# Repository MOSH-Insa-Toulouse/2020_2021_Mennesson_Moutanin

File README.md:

# Kicad Practical TP / Communicating gas sensor

## KiCad - Shield for Arduino

### TODO Kicad

- [x] Create Kicad project
- [x] Design the circuit board
- [x] Assign the components footprints
- [x] Design of the pcb
- [x] Component placement
- [x] Routing

### Diagram

### Placement and Routing

### 3D View

## Manufacturing and integration of nano-technology sensors

You'll find a datasheet related to the sensor we integrated under >A.I.M.E  

It has been done by Zheng Zhou, Terence Liew, Brice Moutanin and Baptiste Mennesson

## Analog Electronic Labs

The goal of this part was to simulate our sensor and its associated electronic diagram thanks to LTSpice. In order to obtain the cutoff frequencies of the different steps and observe the noise attenuations at 50kHz and at the Nyquist frequency.

### Electronic Diagram

### Gas Sensor

### Characteristics

## Analog Electronic Labs

This part was focused on exploiting the data from the gas sensor. The idea was to interconnect several technologies; recover the data from the sensor using an arduino, process this data with the Arduino software, send it over the LoRa network, retrieve it on The Things Network, and finally display it on a dashboard thanks to a Node-Red flow.  

You'll find all the related files under >MOSH>LoRa_Small_Project

### Node-Red Flow Example (Temperature Data)

### Dashboard Example (Temperature Data)

## Contribution

### Students 

* Baptiste MENNESSON
* Brice MOUTANIN

### Tutors

* Jérémie GRISOLIA
* Arnauld BIGANZOLI 
* Benjamin MESTRE

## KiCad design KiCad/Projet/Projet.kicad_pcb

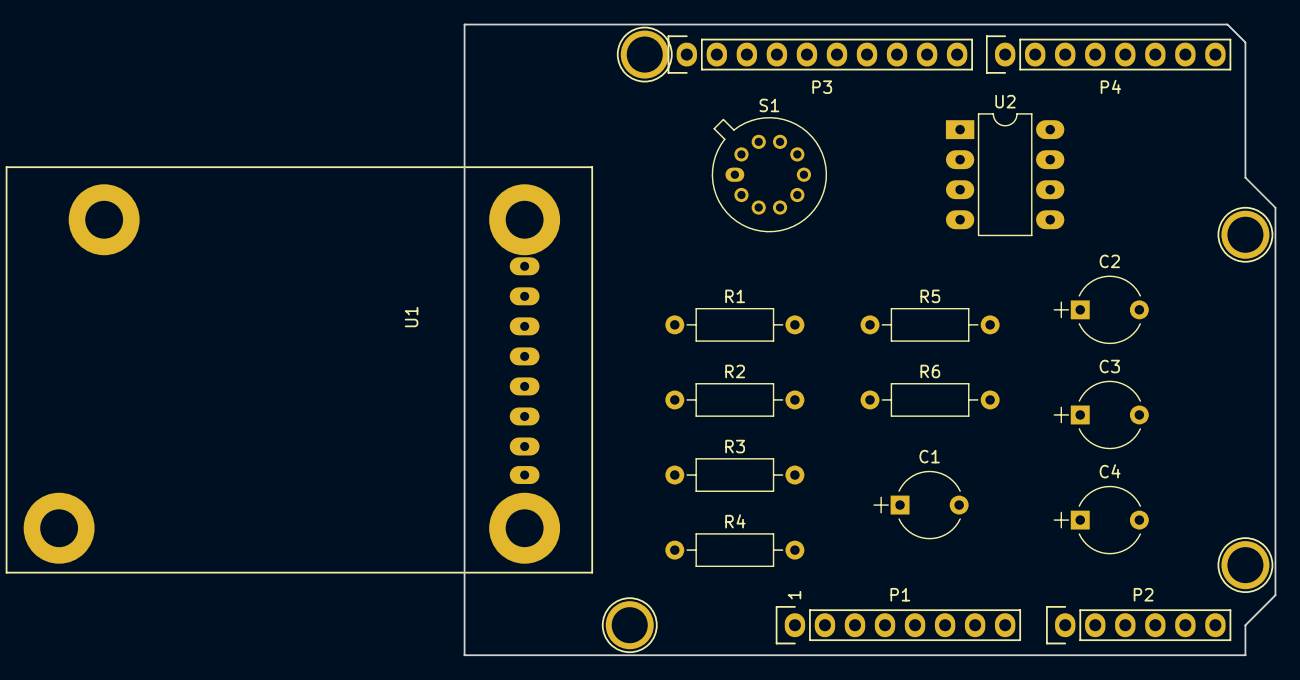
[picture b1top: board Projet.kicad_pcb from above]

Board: 2 copper layers, 68.6 x 53.3 mm, 21 parts (0 on the bottom side), 3 nets, no tracks yet.

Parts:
C1, C2, C3, C4: CP_Radial_Tantal_D5.5mm_P5.00mm
P1: Power; Socket_Strip_Arduino_1x08
P2: Analog; Socket_Strip_Arduino_1x06
P3: Digital; Socket_Strip_Arduino_1x10
P4: Digital; Socket_Strip_Arduino_1x08
P5, P6, P7, P8: CONN_01X01; Arduino_1pin
R1, R2, R3, R4, R5, R6: R_Axial_DIN0207_L6.3mm_D2.5mm_P10.16mm_Horizontal
S1: TO-5-10_Window; Empreinte_Capteur_Gaz
U1: RN2483_breakout
U2: DIP-8_W7.62mm_LongPads; Package_DIP-8_W7.62mm_LongPads

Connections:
/A4(SDA): P2.5, P3.2
/A5(SCL): P2.6, P3.1
GND: P1.6, P1.7, P3.4

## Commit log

2020-12-13 Ajout des dossiers de travail et des fichiers
2020-12-13 Empreinte Capteur Gaz
2020-12-13 Ajout Empreinte + Symbole RN2483
2020-12-22 Ajouts dans le .sch + Implémentation du symbole du LTC1050
2020-12-26 Ajouts Empreintes Composants
2020-12-28 Modification sch + Placements pcb
2020-12-30 V1 PCB + readme
2020-12-30 correction readme
2021-01-14 Complétion du git
2021-01-16 Modif datasheet
